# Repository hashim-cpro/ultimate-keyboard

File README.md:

# Ultimate-keyboard

A custom **75% (84-key)** mechanical keyboard built from the ground up with **Bluetooth 5.0 wireless & wired USB-C connectivity**, **individually addressable per-key RGB backlighting**, **Kailh MX hot-swap sockets**, and **integrated LiPo battery charging**.

It uses the [nrfmicro](https://github.com/joric/nrfmicro) microcontroller architecture as inspiration. Basically, instead of soldering a separate development board onto the keyboard, I copied the microcontroller schematics, put the **Nordic nRF52840 SoC** (via Ebyte E73 module) directly onto the keyboard's PCB, added battery charging and power management circuitry, and routed the entire PCB myself! At the end of the day, the IC lives right on the keyboard PCB with ample room to route everything cleanly.

---

## 3D Renders & Showcase

|                     Top View                      |              Isometric Side View               |                    Bottom View                     |
| :-----------------------------------------------: | :--------------------------------------------: | :------------------------------------------------: |
|  |  |  |

|                PCB Top Layer                |                 PCB Bottom Layer                 |
| :-----------------------------------------: | :----------------------------------------------: |
|  |  |

---

## Project Directory Map

```
ultimate-keyboard/
├── .github/
│   └── workflows/
│       └── build.yml               # Automated ZMK CI build workflow
├── boards/hashim/ultimate_keyboard/ # Zephyr HWMv2 board definition
│   ├── board.yml                   # Board metadata (SoC: nrf52840, variant: zmk)
│   ├── Kconfig.ultimate_keyboard   # Board selection & ZMK_BOARD_COMPAT
│   ├── Kconfig.defconfig           # Name & bootloader retention settings
│   ├── ultimate_keyboard.zmk.yml   # ZMK hardware metadata catalog
│   ├── ultimate_keyboard_nrf52840_zmk.dts # Devicetree definition (matrix, ADC, SPI RGB)
│   └── ultimate_keyboard_nrf52840_zmk_defconfig # Base Kconfig drivers
├── config/
│   ├── ultimate_keyboard.keymap    # 84-key QWERTY + Function layers
│   ├── ultimate_keyboard.conf      # Bluetooth TX power, sleep, RGB underglow
│   └── west.yml                    # Manifest
├── firmware/
│   ├── boards/hashim/ultimate_keyboard/ # Board definition mirror
│   ├── config/                     # Keymap and config mirror
│   ├── build.yaml                  # Firmware build matrix
│   └── ultimate_keyboard.uf2       # Compiled functional flash file (ready to flash)
├── hardware/
│   ├── nrfmicro.kicad_sch
│   ├── nrfmicro.kicad_pcb
│   ├── nrfmicro.kicad_pro
├── exports/
│   ├── gerbers.zip
│   └── others/
│       ├── nrfmicro.csv
│       ├── nrfmicro.step
│       └── nrfmicro board.step
├── media/
├── build.yaml
├── keyboard-layout.json
├── upper plate.dxf
├── journal.md
└── README.md
```

---

## Bill of Materials (BOM)

### 1. Integrated Circuits & Semiconductors

| Designator | Value / Part                                                                                                                  | Package / Footprint          | Qty | Description                                                              |
| :--------- | :---------------------------------------------------------------------------------------------------------------------------- | :--------------------------- | :-: | :----------------------------------------------------------------------- |
| U1         | **[E73-2G4M08S1C](https://www.ebyte.com/en/product-view-news.html?id=445)**                                                   | E73-2G4M08S1C-52840          |  1  | Nordic nRF52840 Bluetooth 5.0 & USB 2.0 SoC Module with PCB Antenna      |
| U2         | **[AP2112K-3.3](https://lcsc.com/product-detail/Low-Dropout-Regulators-LDO_Diodes-Incorporated-AP2112K-3-3TRG1_C51118.html)** | SOT-23-5                     |  1  | 3.3V 600mA Ultra-Low Dropout (LDO) Linear Voltage Regulator              |
| U3         | **[TP4054](https://lcsc.com/product-detail/Battery-Management-ICs_TP4054_C32574.html)**                                       | SOT-23-5                     |  1  | Standalone Linear Li-Ion Battery Charger IC                              |
| U4         | **[74AHCT125](https://lcsc.com/product-detail/Buffers-Drivers-Receivers-Transceivers_Nexperia-74AHCT125D-118_C137151.html)**  | SOIC-14 (3.9x8.7mm, P1.27mm) |  1  | Quad Buffer / 3.3V to 5V Logic Level Shifter for RGB LEDs                |
| Q1, Q2     | **[AO3407](https://lcsc.com/product-detail/MOSFETs_Alpha-Omega-Semicon-AO3407_C13184.html)**                                  | SOT-23                       |  2  | P-Channel 30V MOSFET (Power path switching & battery reverse protection) |
| D100       | **[1N5819](https://lcsc.com/product-detail/Schottky-Barrier-Diodes-SBD_1N5819W_C169344.html)**                                | D_SOD-323F                   |  1  | Schottky Barrier Rectifier Diode (Power OR-ing)                          |
| D200       | **RED LED**                                                                                                                   | LED_0603_1608Metric          |  1  | Red 0603 SMD LED (Battery charge indicator)                              |

### 2. Key Matrix Diodes & Addressable RGB LEDs

| Designator   | Value / Part                                                                                                   | Package / Footprint | Qty | Description                                               |
| :----------- | :------------------------------------------------------------------------------------------------------------- | :------------------ | :-: | :-------------------------------------------------------- |
| D1 – D84     | **[1N4148WT](https://lcsc.com/product-detail/Switching-Diodes_1N4148W_C2128.html)**                            | D_SOD-123           | 84  | High-Speed Switching Diodes (Anti-Ghosting / NKRO Matrix) |
| LED1 – LED84 | **[SK6812MINI-E](https://lcsc.com/product-detail/Light-Emitting-Diodes-LED_HOUEN-SK6812MINI-E_C2890035.html)** | MX_SK6812MINI-E_REV | 84  | Reverse-Mount Individually Addressable RGB LEDs           |

### 3. Kailh MX Hot-Swap Sockets

| Designator        |                                       Key Size                                        | Footprint                 |  Qty   | Target Keys                                           |
| :---------------- | :-----------------------------------------------------------------------------------: | :------------------------ | :----: | :---------------------------------------------------- |
| SW2, SW29, ...    | **[1.00u Socket](https://www.aliexpress.com/w/wholesale-kailh-hot-swap-socket.html)** | SW_Hotswap_Kailh_MX_1.00u |   73   | Standard 1u Alpha, Number, Function & Navigation keys |
| SW75, SW76, SW77  |                                   **1.25u Socket**                                    | SW_Hotswap_Kailh_MX_1.25u |   3    | Left Ctrl, Left Win, Left Alt                         |
| SW45, SW32        |                                   **1.50u Socket**                                    | SW_Hotswap_Kailh_MX_1.50u |   2    | Tab, Backslash (\|)                                   |
| SW47, SW72        |                                   **1.75u Socket**                                    | SW_Hotswap_Kailh_MX_1.75u |   2    | Caps Lock, Right Shift                                |
| SW30              |                                   **2.00u Socket**                                    | SW_Hotswap_Kailh_MX_2.00u |   1    | Backspace                                             |
| SW59, SW61        |                                   **2.25u Socket**                                    | SW_Hotswap_Kailh_MX_2.25u |   2    | Left Shift, Enter                                     |
| SW78              |                                   **6.25u Socket**                                    | SW_Hotswap_Kailh_MX_6.25u |   1    | Spacebar                                              |
| **Total Sockets** |                                                                                       |                           | **84** | Full 75% layout coverage                              |

### 4. Connectors, Switches & Crystal

| Designator | Value / Part                                                                                                                                | Package / Footprint                   | Qty | Description                                                    |
| :--------- | :------------------------------------------------------------------------------------------------------------------------------------------ | :------------------------------------ | :-: | :------------------------------------------------------------- |
| J1         | **[USB-C Receptacle 16-pin](https://lcsc.com/product-detail/USB-Connectors_SHOU-HAN-TYPE-C-16PIN_C319133.html)**                            | USB-C_C168688                         |  1  | USB Type-C Receptacle (16-Pin)                                 |
| J2         | **Conn_01x04**                                                                                                                              | connector_swd                         |  1  | 4-Pin SWD Header (VDD, SWDIO, SWCLK, GND)                      |
| J3         | **Conn_01x02**                                                                                                                              | PinSocket_1x02_P1.27mm_Vertical       |  1  | 2-Pin Battery Header (for LiPo battery)                        |
| SW85       | **[Tactile Switch](https://lcsc.com/product-detail/Tactile-Switches_ALPS-ALPINE-SKRK-series_C2665793.html)**                                | SW_Push_SPST_NO_Alps_SKRK             |  1  | Tactile Push Button (Reset / Bootloader mode)                  |
| RESET      | **TestPoint**                                                                                                                               | TestPoint_THTPad_1.0x1.0mm_Drill0.5mm |  1  | Hardware Reset Test Point                                      |
| X1         | **[32.768kHz Crystal](https://lcsc.com/product-detail/Crystals_Micro-Crystal-Switzerland-CM9V-T1A-32-768kHz-7pF-20PPM-TA-QC_C347311.html)** | CM9V-T1A-2Pin_1.6x1.0mm               |  1  | MicroCrystal CM9V-T1A low-frequency crystal for BLE sleep mode |

### 5. Resistors (SMD 0603)

| Designator |   Value   | Footprint         | Qty | Function / Notes                                               |
| :--------- | :-------: | :---------------- | :-: | :------------------------------------------------------------- |
| R1         | **100kΩ** | R_0603_1608Metric |  1  | Pull-up / Gate bias resistor                                   |
| R2, R3     | **5.1kΩ** | R_0603_1608Metric |  2  | USB Type-C CC1 / CC2 pull-down resistors (5V host negotiation) |
| R5         | **RPROG** | R_0603_1608Metric |  1  | Charge current setting resistor for TP4054                     |
| R6         | **820kΩ** | R_0603_1608Metric |  1  | Voltage divider bias resistor                                  |
| R7, R9     |  **2MΩ**  | R_0603_1608Metric |  2  | High-impedance battery voltage monitoring divider              |
| R8         |  **1kΩ**  | R_0603_1608Metric |  1  | Current limiting resistor for indicator LED                    |

---

## Wiring Diagram

see in [pdf](/exports/diagrams/keyboard_wiring_diagram.pdf)

## Schematics

## Firmware (ZMK)

The keyboard runs native [ZMK Firmware](https://zmk.dev/) built on the Zephyr RTOS with full support for Bluetooth Low Energy 5.0, USB HID, low-power deep sleep, battery level telemetry, and individually addressable RGB backlighting.

A pre-compiled, tested, ready-to-flash binary is available at: **[`firmware/ultimate_keyboard.uf2`](firmware/ultimate_keyboard.uf2)**

## How to Build the Firmware

### GitHub Actions (Recommended & Automated)

This repository includes a GitHub Actions workflow in [`.github/workflows/build.yml`](.github/workflows/build.yml) configured with ZMK's official build matrix. Every push to `main` automatically triggers a build in the cloud.

1. Edit your keymap in [`config/ultimate_keyboard.keymap`](config/ultimate_keyboard.keymap) or settings in [`config/ultimate_keyboard.conf`](config/ultimate_keyboard.conf).
2. Commit and push your changes:
3. Once the workflow run completes, click into the run, scroll to **Artifacts**, and download `ultimate_keyboard.zip`.
4. Extract the `.uf2` file and flash it!
   > (enter bootloader mode by holding the dedicated button beneath space bar)

---

## Assembly

After getting the PCB and the components, you can assemble the keyboard by following these steps:

- first of all solder the MCU and the ICs surrounding it on the top side of the PCB with a heat gun.
- then solder the usbc port and the boot button and the battery connections header(you can solder the wires directly to the pads if you want).
- then solder the diodes, rgb leds and switch sockets along with everything remaining on the bottom side of the PCB.
- connect the battery, flash the firmware, put the switches in and then you can test the keyboard and make sure everything is working properly.

---

### AI Usage Declaration

I used AI for research, general queries and for asking question like using it instead of google, and formatting the markdown documentation and BOM tables. and fixing firmware as well.

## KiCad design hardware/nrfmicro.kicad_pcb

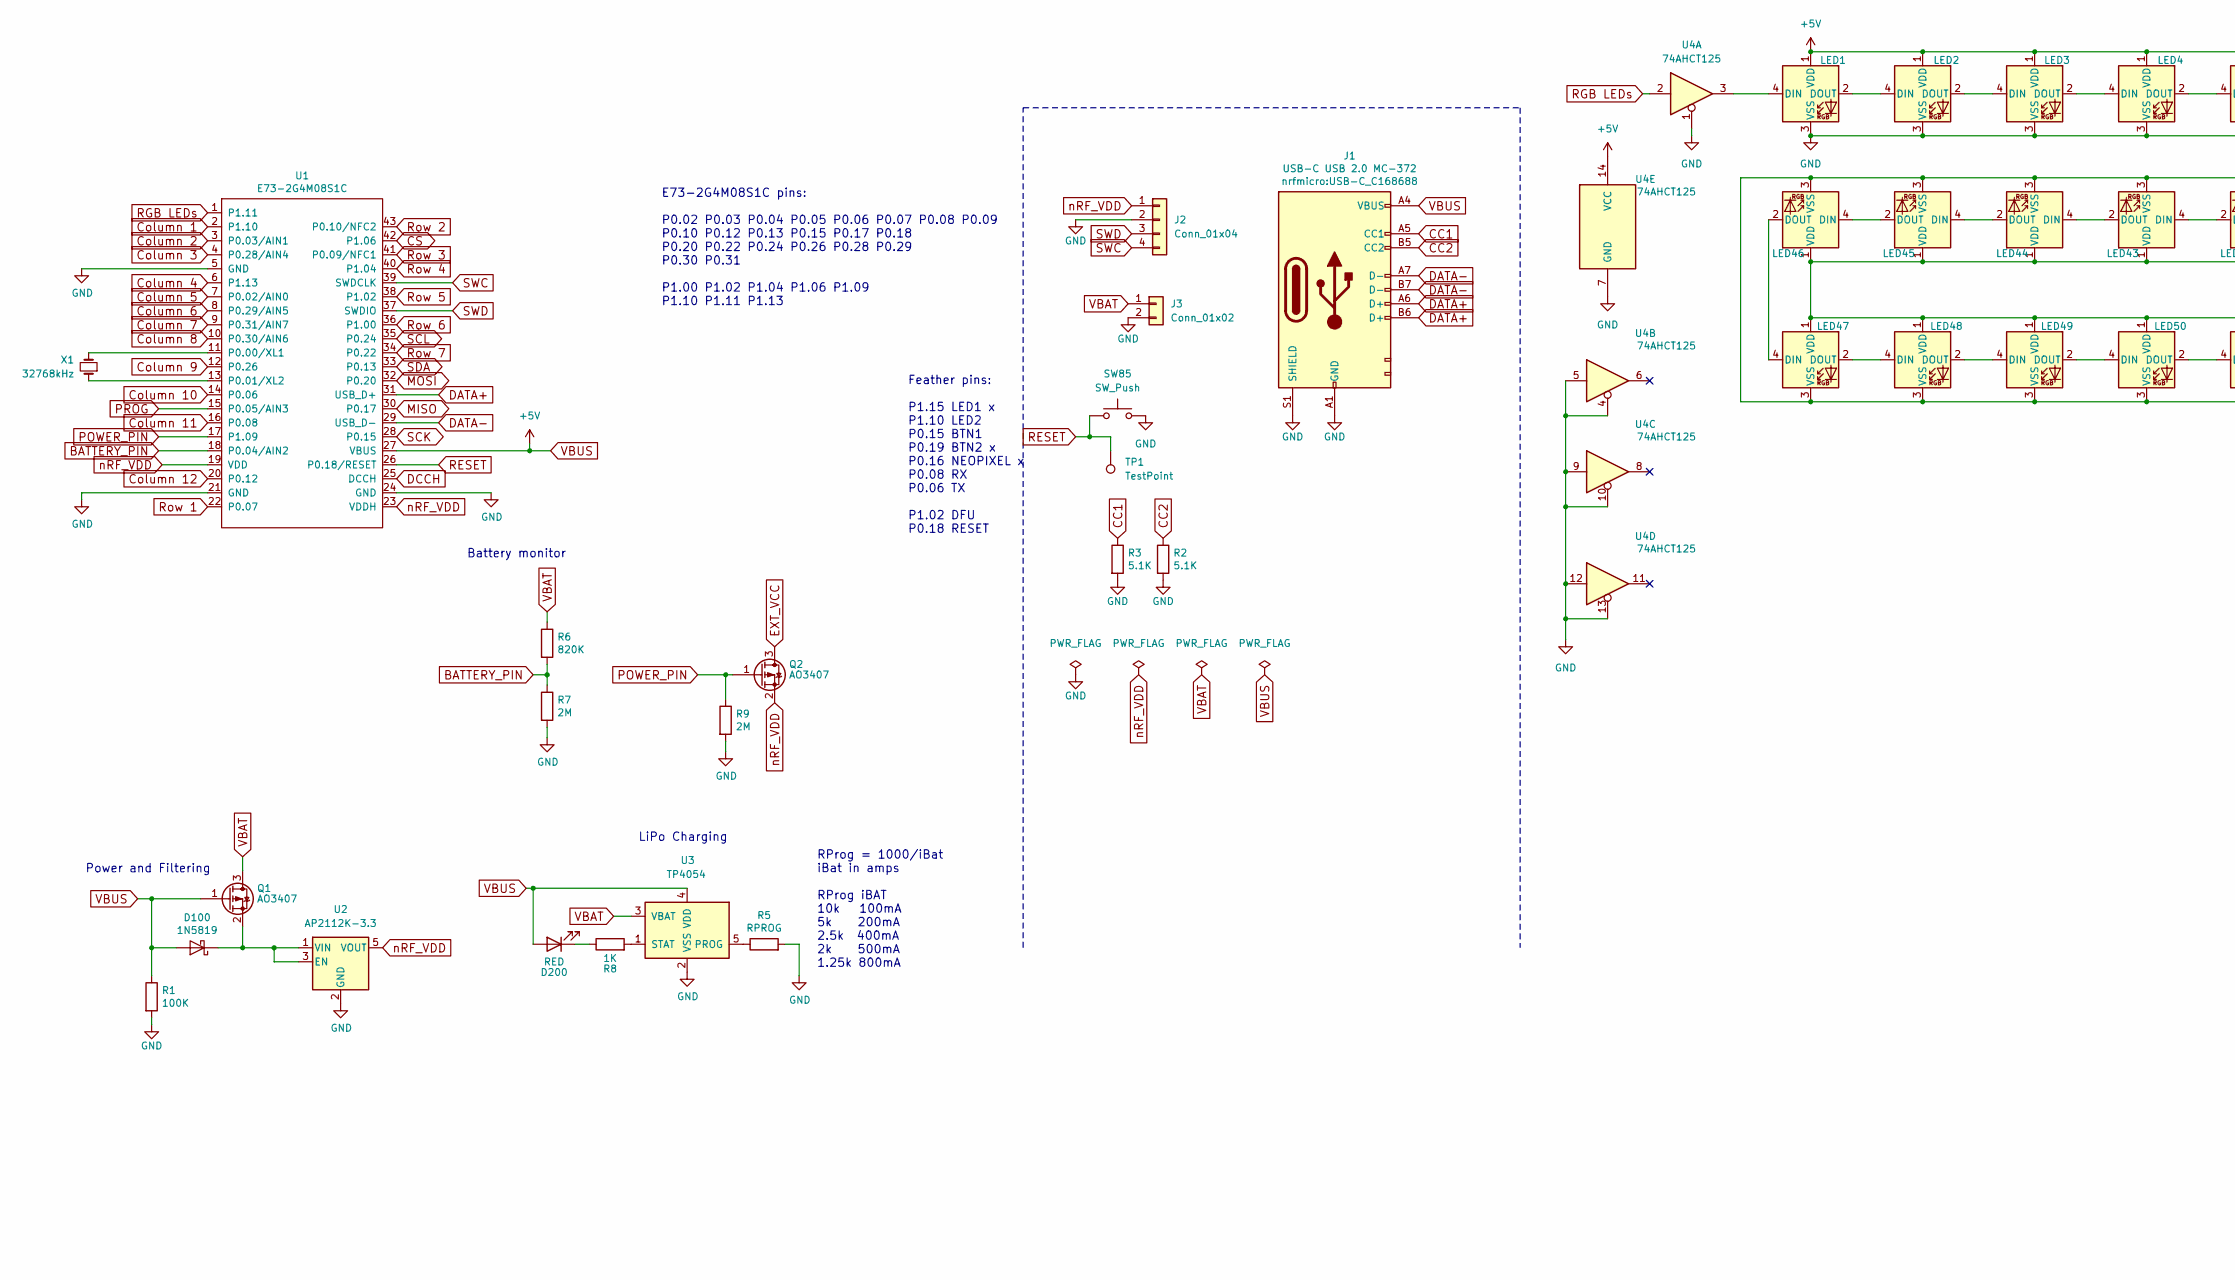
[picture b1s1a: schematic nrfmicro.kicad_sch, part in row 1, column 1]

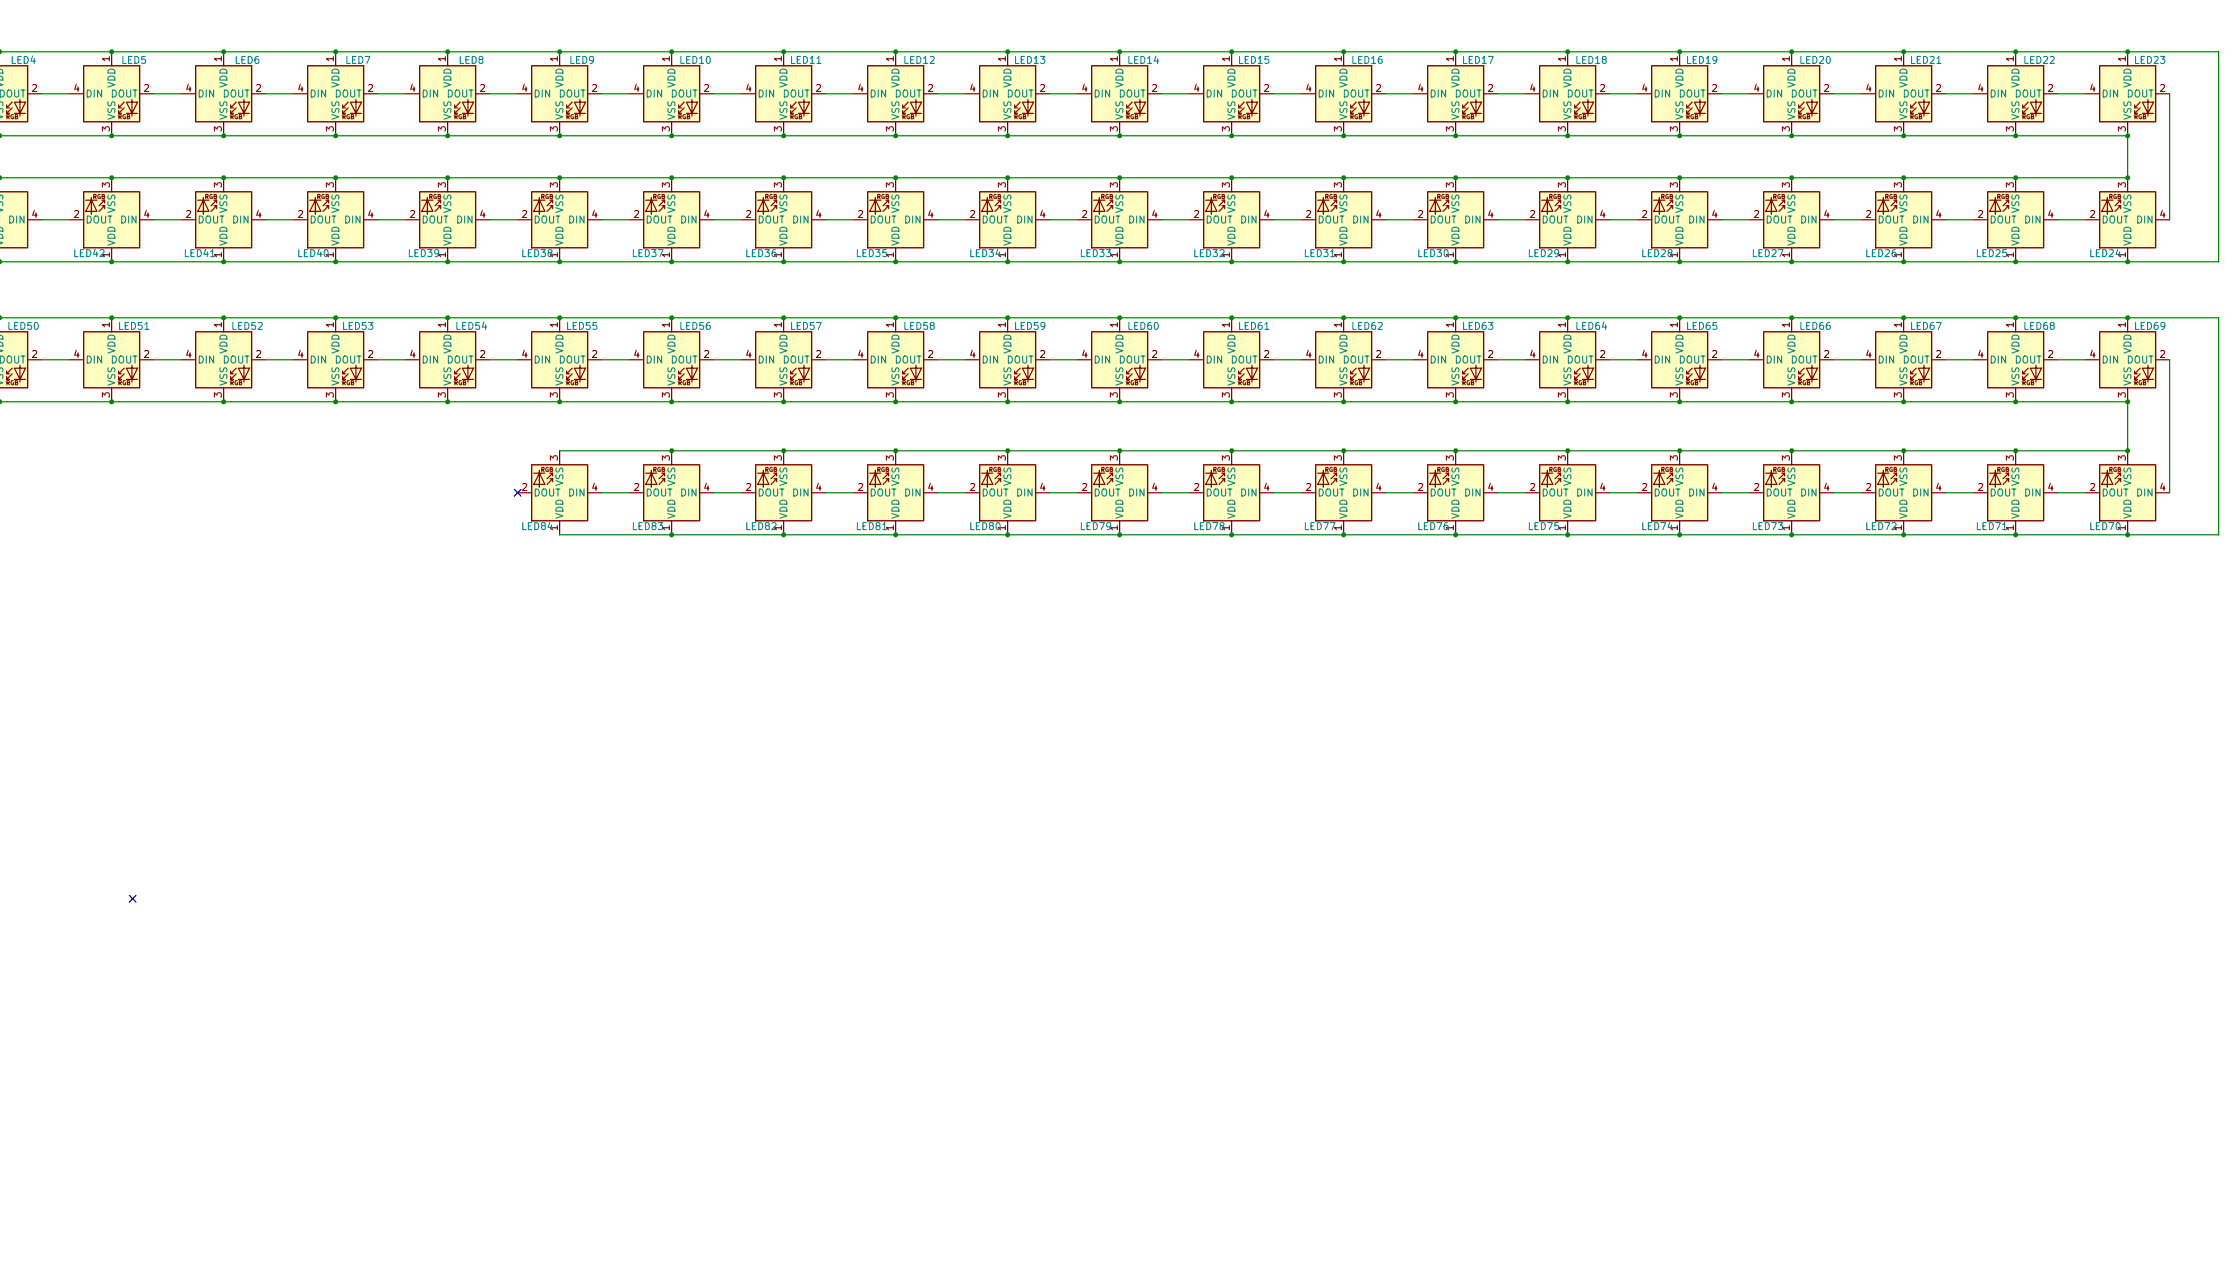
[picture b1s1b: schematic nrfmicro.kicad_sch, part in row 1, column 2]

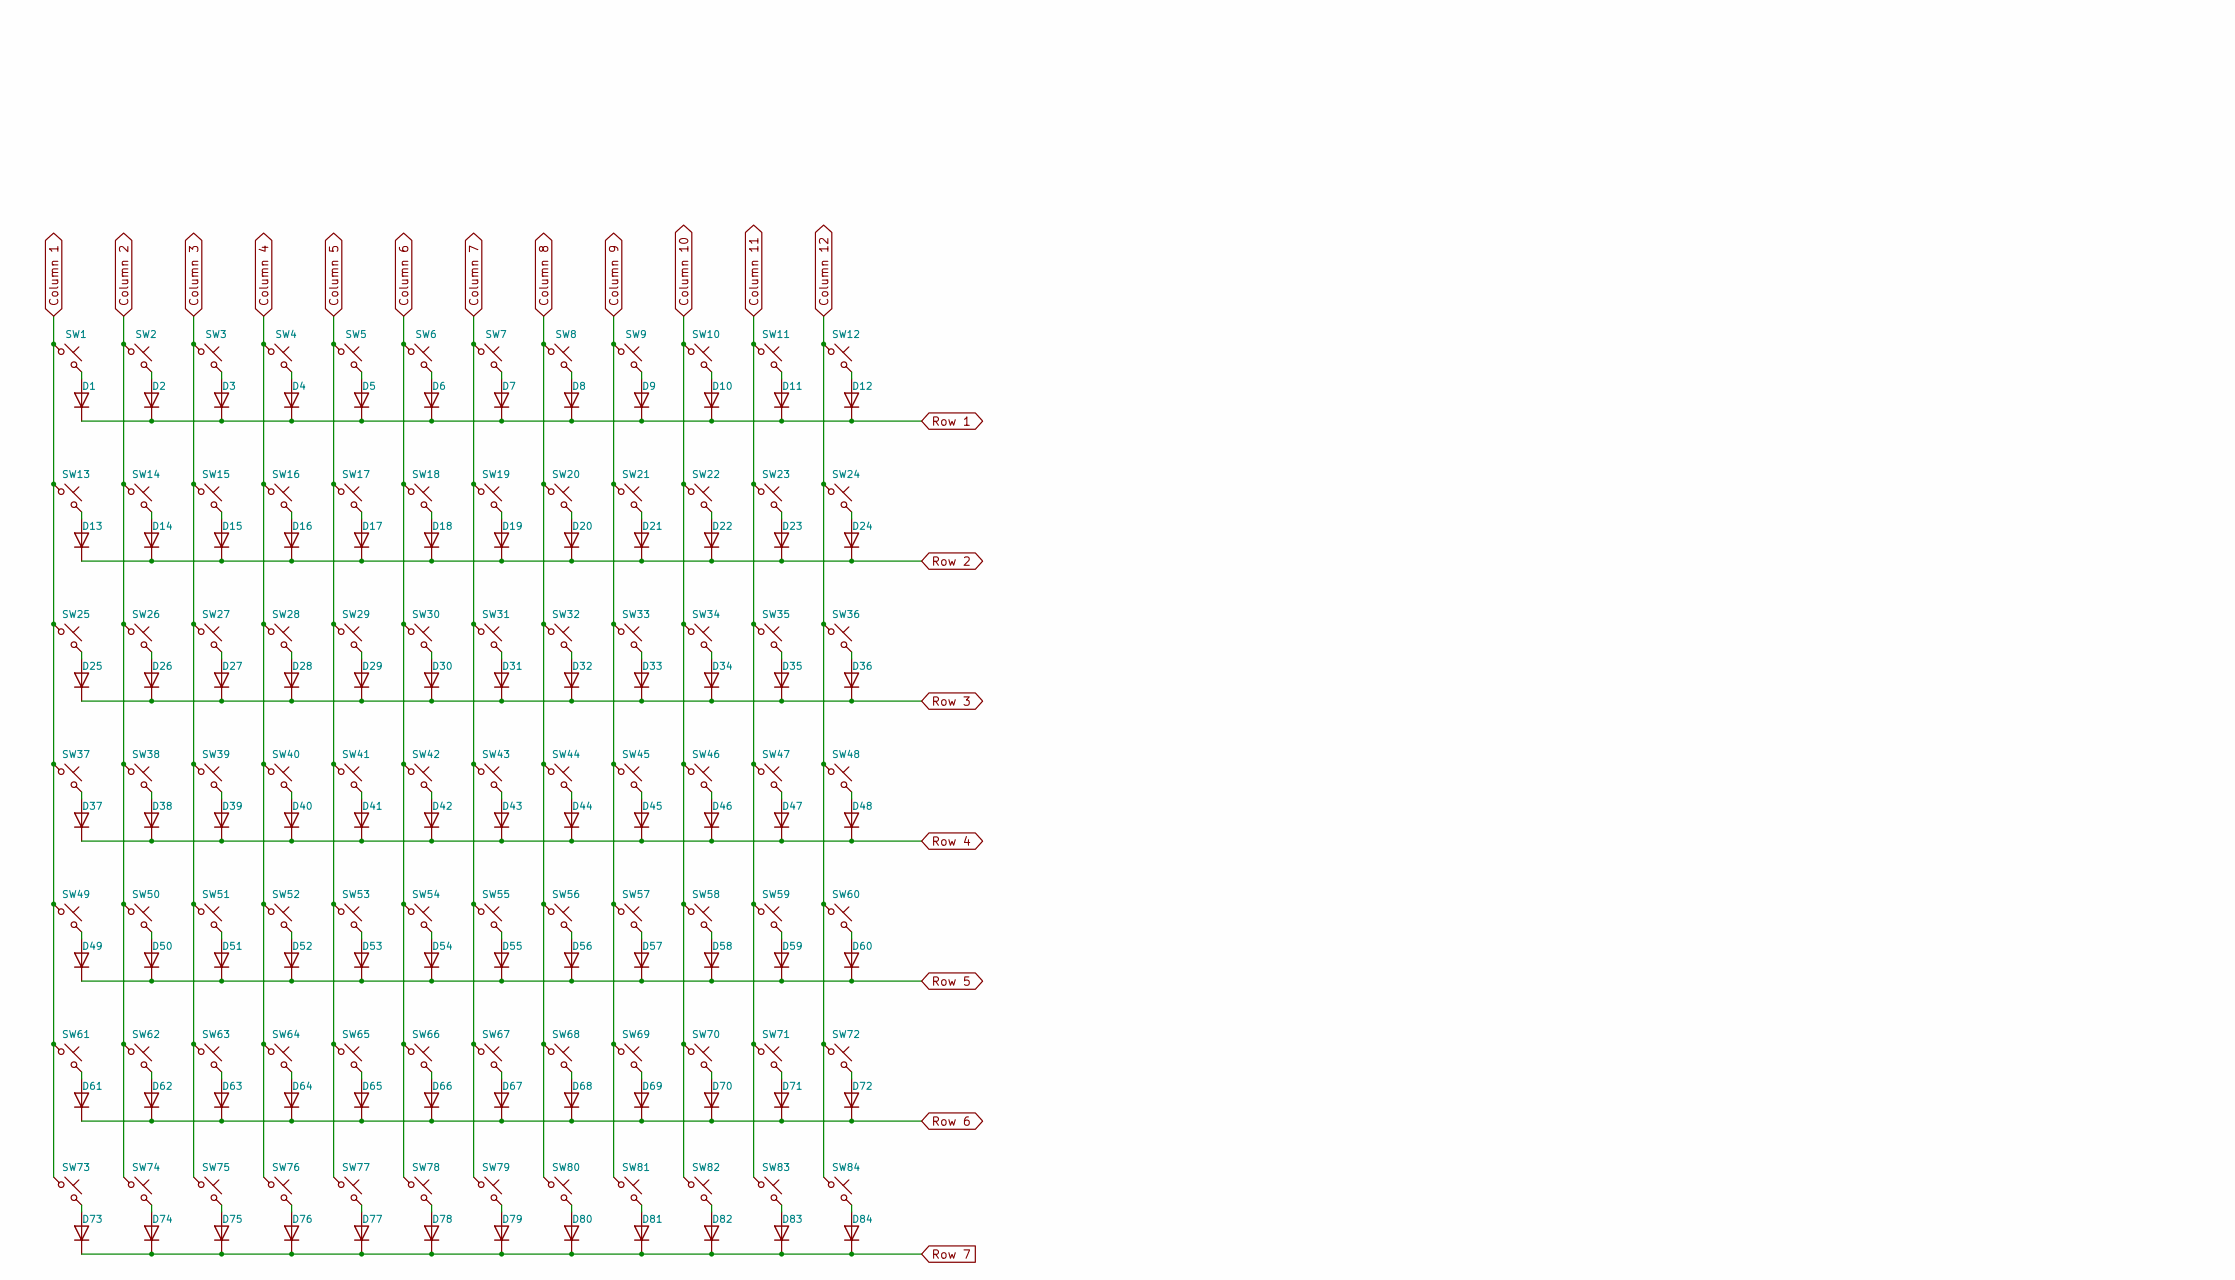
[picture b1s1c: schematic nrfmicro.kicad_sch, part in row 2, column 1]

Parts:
D1, D2, D3, D4, D5, D6, D7, D8, D9, D10, D11, D12, D13, D14, D15, D16, D17, D18, D19, D20, D21, D22, D23, D24, D25, D26, D27, D28, D29, D30, D31, D32, D33, D34, D35, D36, D37, D38, D39, D40, D41, D42, D43, D44, D45, D46, D47, D48, D49, D50, D51, D52, D53, D54, D55, D56, D57, D58, D59, D60, D61, D62, D63, D64, D65, D66, D67, D68, D69, D70, D71, D72, D73, D74, D75, D76, D77, D78, D79, D80, D81, D82, D83, D84: 1N4148WT; D_SOD-123
D100: 1N5819; D_SOD-323F
D200: RED; LED_0603_1608Metric
J1: USB-C USB 2.0 MC-372; USB-C_C168688
J2: Conn_01x04; connector_swd
J3: Conn_01x02; PinSocket_1x02_P1.27mm_Vertical
LED1, LED2, LED3, LED4, LED5, LED6, LED7, LED8, LED9, LED10, LED11, LED12, LED13, LED14, LED15, LED16, LED17, LED18, LED19, LED20, LED21, LED22, LED23, LED24, LED25, LED26, LED27, LED28, LED29, LED30, LED31, LED32, LED33, LED34, LED35, LED36, LED37, LED38, LED39, LED40, LED41, LED42, LED43, LED44, LED45, LED46, LED47, LED48, LED49, LED50, LED51, LED52, LED53, LED54, LED55, LED56, LED57, LED58, LED59, LED60, LED61, LED62, LED63, LED64, LED65, LED66, LED67, LED68, LED69, LED70, LED71, LED72, LED73, LED74, LED75, LED76, LED77, LED78, LED79, LED80, LED81, LED82, LED83, LED84: SK6812MINI-E; MX_SK6812MINI-E_REV
Q1, Q2: AO3407; SOT-23
R1: 100K; R_0603_1608Metric
R2, R3: 5.1K; R_0603_1608Metric
R5: RPROG; R_0603_1608Metric
R6: 820K; R_0603_1608Metric
R7, R9: 2M; R_0603_1608Metric
R8: 1K; R_0603_1608Metric
SW1, SW2, SW3, SW4, SW5, SW6, SW7, SW8, SW9, SW10, SW11, SW12, SW13, SW14, SW15, SW16, SW17, SW18, SW19, SW20, SW21, SW22, SW23, SW24, SW25, SW26, SW27, SW28, SW29, SW31, SW33, SW34, SW35, SW36, SW37, SW38, SW39, SW40, SW41, SW42, SW43, SW44, SW46, SW48, SW49, SW50, SW51, SW52, SW53, SW54, SW55, SW56, SW57, SW58, SW60, SW62, SW63, SW64, SW65, SW66, SW67, SW68, SW69, SW70, SW71, SW73, SW74, SW79, SW80, SW81, SW82, SW83, SW84: SW_Push_45deg; SW_Hotswap_Kailh_MX_1.00u
SW30: SW_Push_45deg; SW_Hotswap_Kailh_MX_2.00u
SW32, SW45: SW_Push_45deg; SW_Hotswap_Kailh_MX_1.50u
SW47, SW72: SW_Push_45deg; SW_Hotswap_Kailh_MX_1.75u
SW59, SW61: SW_Push_45deg; SW_Hotswap_Kailh_MX_2.25u
SW75, SW76, SW77: SW_Push_45deg; SW_Hotswap_Kailh_MX_1.25u
SW78: SW_Push_45deg; SW_Hotswap_Kailh_MX_6.25u
SW85: SW_Push; SW_Push_SPST_NO_Alps_SKRK
TP1: TestPoint; TestPoint_THTPad_1.0x1.0mm_Drill0.5mm
U1: E73-2G4M08S1C; E73-2G4M08S1C-52840
U2: AP2112K-3.3; SOT-23-5
U3: TP4054; SOT-23-5
U4: 74AHCT125; SOIC-14_3.9x8.7mm_P1.27mm
X1: 32768kHz; Crystal_SMD_MicroCrystal_CM9V-T1A-2Pin_1.6x1.0mm_HandSolder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

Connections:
BATTERY_PIN: R6.2, R7.1, U1.18 (P0.04/AIN2)
CC1: J1.A5 (CC1), R3.1
CC2: J1.B5 (CC2), R2.1
CS: U1.42 (P1.06)
Column 1: SW1.1, SW13.1, SW25.1, SW37.1, SW49.1, SW61.1, SW73.1, U1.2 (P1.10)
Column 2: SW2.1, SW14.1, SW26.1, SW38.1, SW50.1, SW62.1, SW74.1, U1.3 (P0.03/AIN1)
Column 3: SW3.1, SW15.1, SW27.1, SW39.1, SW51.1, SW63.1, SW75.1, U1.4 (P0.28/AIN4)
Column 4: SW4.1, SW16.1, SW28.1, SW40.1, SW52.1, SW64.1, SW76.1, U1.6 (P1.13)
Column 5: SW5.1, SW17.1, SW29.1, SW41.1, SW53.1, SW65.1, SW77.1, U1.7 (P0.02/AIN0)
Column 6: SW6.1, SW18.1, SW30.1, SW42.1, SW54.1, SW66.1, SW78.1, U1.8 (P0.29/AIN5)
Column 7: SW7.1, SW19.1, SW31.1, SW43.1, SW55.1, SW67.1, SW79.1, U1.9 (P0.31/AIN7)
Column 8: SW8.1, SW20.1, SW32.1, SW44.1, SW56.1, SW68.1, SW80.1, U1.10 (P0.30/AIN6)
Column 9: SW9.1, SW21.1, SW33.1, SW45.1, SW57.1, SW69.1, SW81.1, U1.12 (P0.26)
Column 10: SW10.1, SW22.1, SW34.1, SW46.1, SW58.1, SW70.1, SW82.1, U1.14 (P0.06)
Column 11: SW11.1, SW23.1, SW35.1, SW47.1, SW59.1, SW71.1, SW83.1, U1.16 (P0.08)
Column 12: SW12.1, SW24.1, SW36.1, SW48.1, SW60.1, SW72.1, SW84.1, U1.20 (P0.12)
DATA+: J1.A6 (D+), J1.B6 (D+), U1.31 (USB_D+)
DATA-: J1.A7 (D-), J1.B7 (D-), U1.29 (USB_D-)
DCCH: U1.25 (DCCH)
EXT_VCC: Q2.3 (D)
GND: J1.A1 (GND), J1.S1 (SHIELD), J2.2, J3.2, LED1.3 (VSS), LED2.3 (VSS), LED3.3 (VSS), LED4.3 (VSS), LED5.3 (VSS), LED6.3 (VSS), LED7.3 (VSS), LED8.3 (VSS), LED9.3 (VSS), LED10.3 (VSS), LED11.3 (VSS), LED12.3 (VSS), LED13.3 (VSS), LED14.3 (VSS), LED15.3 (VSS), LED16.3 (VSS), LED17.3 (VSS), LED18.3 (VSS), LED19.3 (VSS), LED20.3 (VSS), LED21.3 (VSS), LED22.3 (VSS), LED23.3 (VSS), LED24.3 (VSS), LED25.3 (VSS), LED26.3 (VSS), LED27.3 (VSS), LED28.3 (VSS), LED29.3 (VSS), LED30.3 (VSS), LED31.3 (VSS), LED32.3 (VSS), LED33.3 (VSS), LED34.3 (VSS), LED35.3 (VSS), LED36.3 (VSS), LED37.3 (VSS), LED38.3 (VSS), LED39.3 (VSS), LED40.3 (VSS), LED41.3 (VSS), LED42.3 (VSS), LED43.3 (VSS), LED44.3 (VSS), LED45.3 (VSS), LED46.3 (VSS), LED47.3 (VSS), LED48.3 (VSS), LED49.3 (VSS), LED50.3 (VSS), LED51.3 (VSS), LED52.3 (VSS), LED53.3 (VSS), LED54.3 (VSS), LED55.3 (VSS), LED56.3 (VSS), LED57.3 (VSS), LED58.3 (VSS), LED59.3 (VSS), LED60.3 (VSS), LED61.3 (VSS), LED62.3 (VSS), LED63.3 (VSS), LED64.3 (VSS), LED65.3 (VSS), LED66.3 (VSS), LED67.3 (VSS), LED68.3 (VSS), LED69.3 (VSS), LED70.3 (VSS), LED71.3 (VSS), LED72.3 (VSS), LED73.3 (VSS), LED74.3 (VSS), LED75.3 (VSS), LED76.3 (VSS), LED77.3 (VSS), LED78.3 (VSS), LED79.3 (VSS), LED80.3 (VSS), LED81.3 (VSS), LED82.3 (VSS), LED83.3 (VSS), LED84.3 (VSS), R1.2, R2.2, R3.2, R5.2, R7.2, R9.2, SW85.2, U1.5 (GND), U1.21 (GND), U1.24 (GND), U2.2 (GND), U3.2 (VSS), U4.1, U4.4, U4.5, U4.7 (GND), U4.9, U4.10, U4.12, U4.13
MISO: U1.30 (P0.17)
MOSI: U1.32 (P0.20)
unnamed: D1.2 (A), SW1.2
unnamed: D2.2 (A), SW2.2
unnamed: D3.2 (A), SW3.2
unnamed: D4.2 (A), SW4.2
unnamed: D5.2 (A), SW5.2
unnamed: D6.2 (A), SW6.2
unnamed: D7.2 (A), SW7.2
unnamed: D8.2 (A), SW8.2
unnamed: D9.2 (A), SW9.2
unnamed: D10.2 (A), SW10.2
unnamed: D11.2 (A), SW11.2
unnamed: D12.2 (A), SW12.2
unnamed: D13.2 (A), SW13.2
unnamed: D14.2 (A), SW14.2
unnamed: D15.2 (A), SW15.2
unnamed: D16.2 (A), SW16.2
unnamed: D17.2 (A), SW17.2
unnamed: D18.2 (A), SW18.2
unnamed: D19.2 (A), SW19.2
unnamed: D20.2 (A), SW20.2
unnamed: D21.2 (A), SW21.2
unnamed: D22.2 (A), SW22.2
unnamed: D23.2 (A), SW23.2
unnamed: D24.2 (A), SW24.2
unnamed: D25.2 (A), SW25.2
unnamed: D26.2 (A), SW26.2
unnamed: D27.2 (A), SW27.2
unnamed: D28.2 (A), SW28.2
unnamed: D29.2 (A), SW29.2
unnamed: D30.2 (A), SW30.2
unnamed: D31.2 (A), SW31.2
unnamed: D32.2 (A), SW32.2
unnamed: D33.2 (A), SW33.2
unnamed: D34.2 (A), SW34.2
unnamed: D35.2 (A), SW35.2
unnamed: D36.2 (A), SW36.2
unnamed: D37.2 (A), SW37.2
unnamed: D38.2 (A), SW38.2
unnamed: D39.2 (A), SW39.2
unnamed: D40.2 (A), SW40.2
unnamed: D41.2 (A), SW41.2
unnamed: D42.2 (A), SW42.2
unnamed: D43.2 (A), SW43.2
unnamed: D44.2 (A), SW44.2
unnamed: D45.2 (A), SW45.2
unnamed: D46.2 (A), SW46.2
unnamed: D47.2 (A), SW47.2
unnamed: D48.2 (A), SW48.2
unnamed: D49.2 (A), SW49.2
unnamed: D50.2 (A), SW50.2
unnamed: D51.2 (A), SW51.2
unnamed: D52.2 (A), SW52.2
unnamed: D53.2 (A), SW53.2
unnamed: D54.2 (A), SW54.2
unnamed: D55.2 (A), SW55.2
unnamed: D56.2 (A), SW56.2
unnamed: D57.2 (A), SW57.2
unnamed: D58.2 (A), SW58.2
unnamed: D59.2 (A), SW59.2
unnamed: D60.2 (A), SW60.2
unnamed: D61.2 (A), SW61.2
unnamed: D62.2 (A), SW62.2
unnamed: D63.2 (A), SW63.2
unnamed: D64.2 (A), SW64.2
unnamed: D65.2 (A), SW65.2
unnamed: D66.2 (A), SW66.2
unnamed: D67.2 (A), SW67.2
unnamed: D68.2 (A), SW68.2
unnamed: D69.2 (A), SW69.2
unnamed: D70.2 (A), SW70.2
unnamed: D71.2 (A), SW71.2
unnamed: D72.2 (A), SW72.2
unnamed: D73.2 (A), SW73.2
unnamed: D74.2 (A), SW74.2
unnamed: D75.2 (A), SW75.2
unnamed: D76.2 (A), SW76.2
unnamed: D77.2 (A), SW77.2
unnamed: D78.2 (A), SW78.2
unnamed: D79.2 (A), SW79.2
unnamed: D80.2 (A), SW80.2
unnamed: D81.2 (A), SW81.2
unnamed: D82.2 (A), SW82.2
unnamed: D83.2 (A), SW83.2
unnamed: D84.2 (A), SW84.2
unnamed: D100.1 (K), Q1.2 (S), U2.1 (VIN), U2.3 (EN)
unnamed: D200.1 (K), R8.1
unnamed: LED1.4 (DIN), U4.3
unnamed: LED1.2 (DOUT), LED2.4 (DIN)
unnamed: LED2.2 (DOUT), LED3.4 (DIN)
unnamed: LED3.2 (DOUT), LED4.4 (DIN)
unnamed: LED4.2 (DOUT), LED5.4 (DIN)
unnamed: LED5.2 (DOUT), LED6.4 (DIN)
unnamed: LED6.2 (DOUT), LED7.4 (DIN)
unnamed: LED7.2 (DOUT), LED8.4 (DIN)
unnamed: LED8.2 (DOUT), LED9.4 (DIN)
unnamed: LED9.2 (DOUT), LED10.4 (DIN)
unnamed: LED10.2 (DOUT), LED11.4 (DIN)
unnamed: LED11.2 (DOUT), LED12.4 (DIN)
unnamed: LED12.2 (DOUT), LED13.4 (DIN)
unnamed: LED13.2 (DOUT), LED14.4 (DIN)
unnamed: LED14.2 (DOUT), LED15.4 (DIN)
unnamed: LED15.2 (DOUT), LED16.4 (DIN)
unnamed: LED16.2 (DOUT), LED17.4 (DIN)
unnamed: LED17.2 (DOUT), LED18.4 (DIN)
unnamed: LED18.2 (DOUT), LED19.4 (DIN)
unnamed: LED19.2 (DOUT), LED20.4 (DIN)
unnamed: LED20.2 (DOUT), LED21.4 (DIN)
unnamed: LED21.2 (DOUT), LED22.4 (DIN)
unnamed: LED22.2 (DOUT), LED23.4 (DIN)
unnamed: LED23.2 (DOUT), LED24.4 (DIN)
unnamed: LED24.2 (DOUT), LED25.4 (DIN)
unnamed: LED25.2 (DOUT), LED26.4 (DIN)
unnamed: LED26.2 (DOUT), LED27.4 (DIN)
unnamed: LED27.2 (DOUT), LED28.4 (DIN)
unnamed: LED28.2 (DOUT), LED29.4 (DIN)
unnamed: LED29.2 (DOUT), LED30.4 (DIN)
unnamed: LED30.2 (DOUT), LED31.4 (DIN)
unnamed: LED31.2 (DOUT), LED32.4 (DIN)
unnamed: LED32.2 (DOUT), LED33.4 (DIN)
unnamed: LED33.2 (DOUT), LED34.4 (DIN)
unnamed: LED34.2 (DOUT), LED35.4 (DIN)
unnamed: LED35.2 (DOUT), LED36.4 (DIN)
unnamed: LED36.2 (DOUT), LED37.4 (DIN)
unnamed: LED37.2 (DOUT), LED38.4 (DIN)
unnamed: LED38.2 (DOUT), LED39.4 (DIN)
unnamed: LED39.2 (DOUT), LED40.4 (DIN)
unnamed: LED40.2 (DOUT), LED41.4 (DIN)
unnamed: LED41.2 (DOUT), LED42.4 (DIN)
unnamed: LED42.2 (DOUT), LED43.4 (DIN)
unnamed: LED43.2 (DOUT), LED44.4 (DIN)
unnamed: LED44.2 (DOUT), LED45.4 (DIN)
unnamed: LED45.2 (DOUT), LED46.4 (DIN)
unnamed: LED46.2 (DOUT), LED47.4 (DIN)
unnamed: LED47.2 (DOUT), LED48.4 (DIN)
unnamed: LED48.2 (DOUT), LED49.4 (DIN)
unnamed: LED49.2 (DOUT), LED50.4 (DIN)
unnamed: LED50.2 (DOUT), LED51.4 (DIN)
unnamed: LED51.2 (DOUT), LED52.4 (DIN)
unnamed: LED52.2 (DOUT), LED53.4 (DIN)
unnamed: LED53.2 (DOUT), LED54.4 (DIN)
unnamed: LED54.2 (DOUT), LED55.4 (DIN)
unnamed: LED55.2 (DOUT), LED56.4 (DIN)
unnamed: LED56.2 (DOUT), LED57.4 (DIN)
unnamed: LED57.2 (DOUT), LED58.4 (DIN)
unnamed: LED58.2 (DOUT), LED59.4 (DIN)
unnamed: LED59.2 (DOUT), LED60.4 (DIN)
unnamed: LED60.2 (DOUT), LED61.4 (DIN)
unnamed: LED61.2 (DOUT), LED62.4 (DIN)
unnamed: LED62.2 (DOUT), LED63.4 (DIN)
unnamed: LED63.2 (DOUT), LED64.4 (DIN)
unnamed: LED64.2 (DOUT), LED65.4 (DIN)
unnamed: LED65.2 (DOUT), LED66.4 (DIN)
unnamed: LED66.2 (DOUT), LED67.4 (DIN)
unnamed: LED67.2 (DOUT), LED68.4 (DIN)
unnamed: LED68.2 (DOUT), LED69.4 (DIN)
unnamed: LED69.2 (DOUT), LED70.4 (DIN)
unnamed: LED70.2 (DOUT), LED71.4 (DIN)
unnamed: LED71.2 (DOUT), LED72.4 (DIN)
unnamed: LED72.2 (DOUT), LED73.4 (DIN)
unnamed: LED73.2 (DOUT), LED74.4 (DIN)
unnamed: LED74.2 (DOUT), LED75.4 (DIN)
unnamed: LED75.2 (DOUT), LED76.4 (DIN)
unnamed: LED76.2 (DOUT), LED77.4 (DIN)
unnamed: LED77.2 (DOUT), LED78.4 (DIN)
unnamed: LED78.2 (DOUT), LED79.4 (DIN)
unnamed: LED79.2 (DOUT), LED80.4 (DIN)
unnamed: LED80.2 (DOUT), LED81.4 (DIN)
unnamed: LED81.2 (DOUT), LED82.4 (DIN)
unnamed: LED82.2 (DOUT), LED83.4 (DIN)
unnamed: LED83.2 (DOUT), LED84.4 (DIN)
unnamed: U1.11 (P0.00/XL1), X1.2
unnamed: U1.13 (P0.01/XL2), X1.1
unnamed: R5.1, U3.5 (PROG)
unnamed: R8.2, U3.1 (STAT)
POWER_PIN: Q2.1 (G), R9.1, U1.17 (P1.09)
PROG: U1.15 (P0.05/AIN3)
RESET: SW85.1, TP1.1, U1.26 (P0.18/RESET); also elsewhere on the board
RGB LEDs: U1.1 (P1.11), U4.2
Row 1: D1.1 (K), D2.1 (K), D3.1 (K), D4.1 (K), D5.1 (K), D6.1 (K), D7.1 (K), D8.1 (K), D9.1 (K), D10.1 (K), D11.1 (K), D12.1 (K), U1.22 (P0.07)
Row 2: D13.1 (K), D14.1 (K), D15.1 (K), D16.1 (K), D17.1 (K), D18.1 (K), D19.1 (K), D20.1 (K), D21.1 (K), D22.1 (K), D23.1 (K), D24.1 (K), U1.43 (P0.10/NFC2)
Row 3: D25.1 (K), D26.1 (K), D27.1 (K), D28.1 (K), D29.1 (K), D30.1 (K), D31.1 (K), D32.1 (K), D33.1 (K), D34.1 (K), D35.1 (K), D36.1 (K), U1.41 (P0.09/NFC1)
Row 4: D37.1 (K), D38.1 (K), D39.1 (K), D40.1 (K), D41.1 (K), D42.1 (K), D43.1 (K), D44.1 (K), D45.1 (K), D46.1 (K), D47.1 (K), D48.1 (K), U1.40 (P1.04)
Row 5: D49.1 (K), D50.1 (K), D51.1 (K), D52.1 (K), D53.1 (K), D54.1 (K), D55.1 (K), D56.1 (K), D57.1 (K), D58.1 (K), D59.1 (K), D60.1 (K), U1.38 (P1.02)
Row 6: D61.1 (K), D62.1 (K), D63.1 (K), D64.1 (K), D65.1 (K), D66.1 (K), D67.1 (K), D68.1 (K), D69.1 (K), D70.1 (K), D71.1 (K), D72.1 (K), U1.36 (P1.00)
Row 7: D73.1 (K), D74.1 (K), D75.1 (K), D76.1 (K), D77.1 (K), D78.1 (K), D79.1 (K), D80.1 (K), D81.1 (K), D82.1 (K), D83.1 (K), D84.1 (K), U1.34 (P0.22)
SCK: U1.28 (P0.15)
SCL: U1.35 (P0.24)
SDA: U1.33 (P0.13)
SWC: J2.4, U1.39 (SWDCLK)
SWD: J2.3, U1.37 (SWDIO)
VBAT: J3.1, Q1.3 (D), R6.1, U3.3 (VBAT)
VBUS: D100.2 (A), D200.2 (A), J1.A4 (VBUS), LED1.1 (VDD), LED2.1 (VDD), LED3.1 (VDD), LED4.1 (VDD), LED5.1 (VDD), LED6.1 (VDD), LED7.1 (VDD), LED8.1 (VDD), LED9.1 (VDD), LED10.1 (VDD), LED11.1 (VDD), LED12.1 (VDD), LED13.1 (VDD), LED14.1 (VDD), LED15.1 (VDD), LED16.1 (VDD), LED17.1 (VDD), LED18.1 (VDD), LED19.1 (VDD), LED20.1 (VDD), LED21.1 (VDD), LED22.1 (VDD), LED23.1 (VDD), LED24.1 (VDD), LED25.1 (VDD), LED26.1 (VDD), LED27.1 (VDD), LED28.1 (VDD), LED29.1 (VDD), LED30.1 (VDD), LED31.1 (VDD), LED32.1 (VDD), LED33.1 (VDD), LED34.1 (VDD), LED35.1 (VDD), LED36.1 (VDD), LED37.1 (VDD), LED38.1 (VDD), LED39.1 (VDD), LED40.1 (VDD), LED41.1 (VDD), LED42.1 (VDD), LED43.1 (VDD), LED44.1 (VDD), LED45.1 (VDD), LED46.1 (VDD), LED47.1 (VDD), LED48.1 (VDD), LED49.1 (VDD), LED50.1 (VDD), LED51.1 (VDD), LED52.1 (VDD), LED53.1 (VDD), LED54.1 (VDD), LED55.1 (VDD), LED56.1 (VDD), LED57.1 (VDD), LED58.1 (VDD), LED59.1 (VDD), LED60.1 (VDD), LED61.1 (VDD), LED62.1 (VDD), LED63.1 (VDD), LED64.1 (VDD), LED65.1 (VDD), LED66.1 (VDD), LED67.1 (VDD), LED68.1 (VDD), LED69.1 (VDD), LED70.1 (VDD), LED71.1 (VDD), LED72.1 (VDD), LED73.1 (VDD), LED74.1 (VDD), LED75.1 (VDD), LED76.1 (VDD), LED77.1 (VDD), LED78.1 (VDD), LED79.1 (VDD), LED80.1 (VDD), LED81.1 (VDD), LED82.1 (VDD), LED83.1 (VDD), LED84.1 (VDD), Q1.1 (G), R1.1, U1.27 (VBUS), U3.4 (VDD), U4.14 (VCC)
nRF_VDD: J2.1, Q2.2 (S), U1.19 (VDD), U1.23 (VDDH), U2.5 (VOUT)

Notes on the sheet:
LiPo Charging
RProg = 1000/iBat iBat in amps RProg iBAT 10k 100mA 5k 200mA 2.5k 400mA 2k 500mA 1.25k 800mA
Power and Filtering
Battery monitor
E73-2G4M08S1C pins: P0.02 P0.03 P0.04 P0.05 P0.06 P0.07 P0.08 P0.09 P0.10 P0.12 P0.13 P0.15 P0.17 P0.18 P0.20 P0.22 P0.24 P0.26 P0.28 P0.29 P0.30 P0.31 P1.00 P1.02 P1.04 P1.06 P1.09 P1.10 P1.11 P1.13
Feather pins: P1.15 LED1 x P1.10 LED2 P0.15 BTN1 P0.19 BTN2 x P0.16 NEOPIXEL x P0.08 RX P0.06 TX P1.02 DFU P0.18 RESET

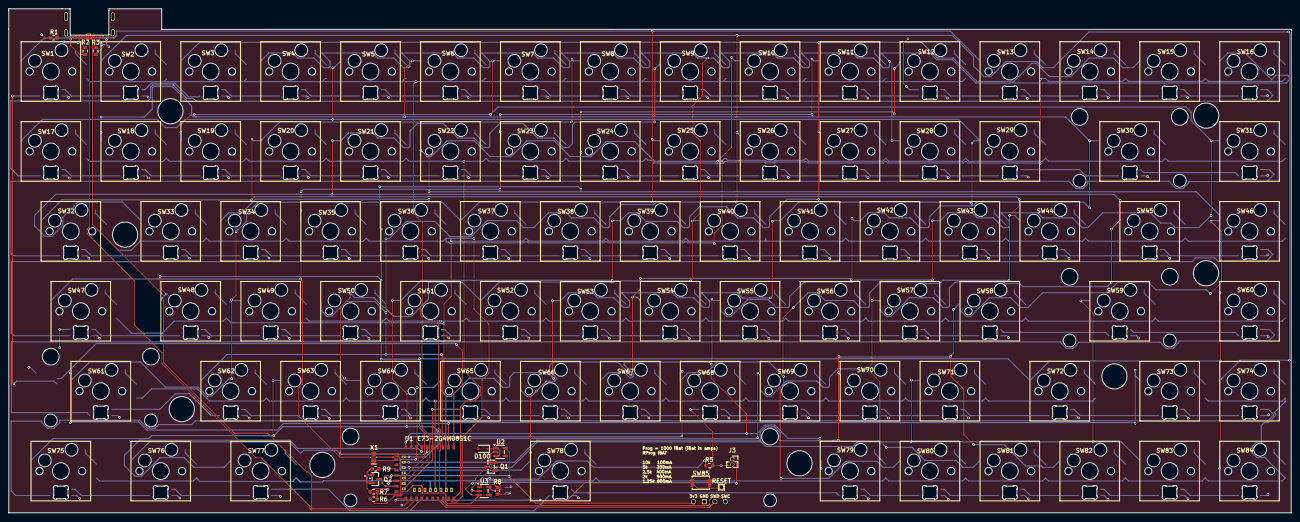
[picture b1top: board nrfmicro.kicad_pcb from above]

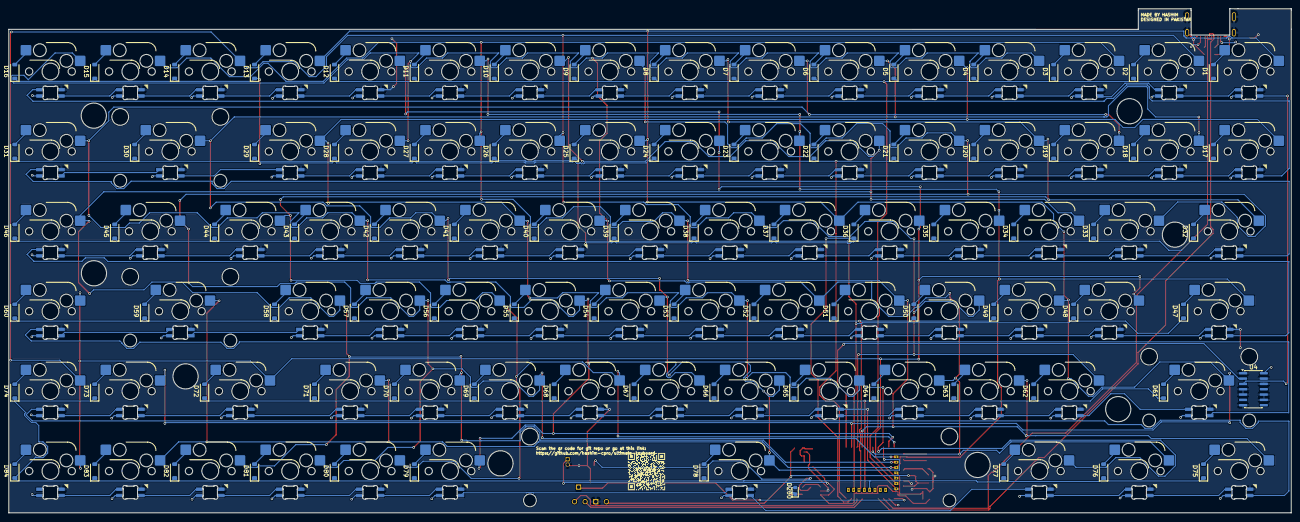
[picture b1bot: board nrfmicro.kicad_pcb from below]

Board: 2 copper layers, 305.8 x 120.2 mm, 274 parts (86 on the bottom side), 207 nets.

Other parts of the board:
RESET: TestPoint; TestPoint_THTPad_1.0x1.0mm_Drill0.5mm

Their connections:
RESET: RESET.1; also elsewhere on the board
